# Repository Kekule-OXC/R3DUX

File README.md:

## About this Repository
This is an open source recreation of one of the most well known Original Xbox LPC memory/IO device created by Team Xecuter, the X3/X3-CE.

The VHDL is 100% compatible with All the original TX software including Flashbios and LiveConfig. This allows loading user BIOS binaries and some basic Xbox tools (EEPROM Backup/modification, Hard drive Rebuilding, Locking, Unlocking, FTP access, as well as customizing the colors of the boot animation).  
  
The VHDL written by Team Xecuter was never released and the CPLD is read protected so it is not trivial to extract the bitstream (and they mislabelled the CPLD to make it even more difficult)

While the VHDL is most likely quite different that what was written originally for the X3 my VHDL implementation is fully compatible with all the features of the original chip.
## Background
The R3DUX chip started off as the OpenX3 project in January 2020 with four members of the discussion group for the RE effort, myself (Kekule)  [Team-Donkey](https://github.com/bolwire),  [Ryzee119](https://github.com/Ryzee119),  and [Ernegien](https://github.com/Ernegien).  

We worked for several months and KingLuxor and I completed a schematic based on the original purple X3 chip ([which he released in 2020](https://github.com/bolwire/OpenX3_Public))  with all of their help we identified the components of the PCB and, KingLuxor did the initial part placement, and I did the PCB layout of our initial OpenX3 chip.  

After verifying that the PCB worked (by transplanting all components from a working X3 chip)  the world was hit by the pandemic, and COVID and real life caused the project to fall aside.    

Ergenien was able to extract the majority of the register information need to complete the design, but the real life time demands of virtual work and school there was no time to even start working on the CPLD code.  
 
Time passed and we all went our separate ways, and so with a known working PCB in hand, and a trove of information we had amassed, the project was abandoned.

Fast forward about six months and I decided to start working on it again, and breathed new life into the project, a REDUX as it were.

## Supported Features

R3DUX Features: 

* Purple board color
* Comes from pre-flashed with FlashBIOS utility
* 2MB Flash ROM; can set up 8x256k, 4x512k, 2x1024k or a single 2048k banks
* Dedicated 256k Backup Rom (can be upgraded) 
* i2c Bus for X3 Config LIVE interface to the EEPROM! 
* I/O Bus for Full LCD support 
* Flash Protection Control 
* Mod Enable - Quick Press Power to boot from 2Mb Flash Rom (External LED will indicate BLUE LED) 
* Mod Disable - Press Power >1 second (External LED will indicate RED LED) 
* Quick Press Power+Eject >1 second to boot from 256k Backup Rom (External LED will indicate PURPLE LED) 
* HDD and LAN Activity LEDs
* D0 Control (Disable Mod Via Software) 
* R3DUX works without any switch accessories connected (boots to the first 1MB bank)
* Compatible with all BIOSes 

LCD-Specific Features:
* Custom text Display on boot 
* Display X3 Config Live Version 
* Display Dip switch and selected BIOS
* XBMC and Avalaunch LCD features are compatible

A mix of features from the purple and CE editions
* XLCD connector is a right angle instead of straight
* Single Pinheader for 5v connection on a v1.6 xbox
* Porgramming pins rerouted to the 4 unused pins on the LCD connector instead of test points

## Installation and Initial Setup
Installation is identical to an OEM X3 chip, and all connections are fully compatible so can be used plug and play with a previous X3 install.
 
 Before assembling the board, you must 
 * 1- Program the backup chip with a 256k Flashbios.... 
 * 2- program the main flash chip with a 2MB Flashbios (8 copies).... 
 * 3- program the EEPROM
 * CPLD programming points are wired to the LCD connector (see images folder)
 * JED can be compiled from ISP Lever
See [Installation.MD] for more details

## Licensing
R3DUX gerbers and schematic are free and open source. Please respect the licenses available in their respective folders.
  *  Hardware is shared under the [CERN OHL version 1.2.](https://ohwr.org/cernohl).
  *  Firmware is shared under [GPLv3](https://www.gnu.org/licenses/quick-guide-gplv3.en.html).
 
## References that helped me in this project
  * [Intel LPC Spec](https://www.intel.com/content/dam/www/program/design/us/en/documents/low-pin-count-interface-specification.pdf)
  * [LPC Analyser Plugin](https://github.com/Ryzee119/LPCAnalyzer)  
  * [Deconstructing the Xbox Boot ROM](https://mborgerson.com/deconstructing-the-xbox-boot-rom/)

By Kekule

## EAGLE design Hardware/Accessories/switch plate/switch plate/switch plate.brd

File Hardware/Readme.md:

| Qty | Value                   | Device           | Package                    | Parts          | Description                 | DigiKey Part         |
|-----|-------------------------|------------------|----------------------------|----------------|-----------------------------|----------------------|
| 2   | Blue                    | LED              | 805                        | LED1, LED2     | LED                         | 1516-1083-1-ND       |
| 1   |                         | PINHD-1X1        | 1X01                       | JP2            | PIN HEADER                  |                      |
| 1   |                         | PINHD-2X8        | 2X08                       | JP1            | PIN HEADER                  |                      |
| 1   | 0                       | Resistor         | 0603                       | R7             | 0ohm resistor               | 541-3927-1-ND        |
| 2   | 0.1uF                   | CAP              | 603                        | C1, C2         |  Ceramic Capacitors         | 720-1689-1-ND        |
| 1   | 0532610271              | 2P connector     | MOLEX_0532610271           | J3             | 1.25mm Pitch PicoBlade      | WM7620CT-ND          |
| 1   | 0532610371              | 3P connector     | MOLEX_0532610371           | J4             | 1.25mm Pitch PicoBlade      | WM7621CT-ND          |
| 1   | 100                     | RES ARRAY        | 0603-ARV                   | RN3            | Array Chip Resistor         | 42X083101JPCT-ND     |
| 3   | 10k                     | RES              | 0603                       | R5, R6, R8     | 10kohm resistor             | PAT10KACT-ND         |
| 2   | 10k                     | RES ARRAY        | 0603-ARV                   | RN1, RN2       | Array Chip Resistor         | TC164J-10KCT-ND      |
| 2   | 200                     | RES              | 0603                       | R9, R10        | 200ohm resistor             | P200GCT-ND           |
| 1   | AT24C08                 | EEPROM           | SO-08                      | IC1            | Serial EEPROM               | AT24C08D-SSHM-B-ND   |
| 1   | 4.7k                    | RES              | 0603                       | R12            | 4.7kohm resistor            | 541-3689-1-ND        |
| 1   | AM29F002BB90EI          | FLASH            | TS032                      | U3             | NOR Flash 5V 2Mbit          | -----                |
| 1   | AM29F016D-70EF          | FLASH            | SOP50P2000X120-48N         | U2             | NOR Flash 5V 16Mbit         | -----                |
| 1   | 10k                     | POT              | TRIM_F09                   | R11            | Thumbwheel Pot 10mm         | -----                |
| 1   | LC4256V-75TN100C        | LC4256V-75TN100C | TQFP100                    | U1             | Lattice MACH4000 CPLD 256MC | 220-1706-ND          |
| 1   | PCM12SMTR               | PCM12SMTR        | SW_PCM12SMTR               | S1             | SPDT Side                   | 401-2016-1-ND        |
| 4   | SI1967DH-T1-GE3         | PNP-Transistor   | TRANS_UM6J1-L              | R1, R2, R3, R4 |                             | SI1967DH-T1-GE3CT-ND |
| 1   | SM12B-SRSS-TB(LF)(SN)   | 12P JST          | CONN_SM12B-SRSS-TB(LF)(SN) | J2             |                             | 455-1812-1-ND        |
| 1   | SM20B-SRDS-G-TF(LF)(SN) | 20P JST          | SM20BSRDSGTFLFSN           | J1             | JST SHD, 1mm Pitch          | 455-1866-1-ND        |

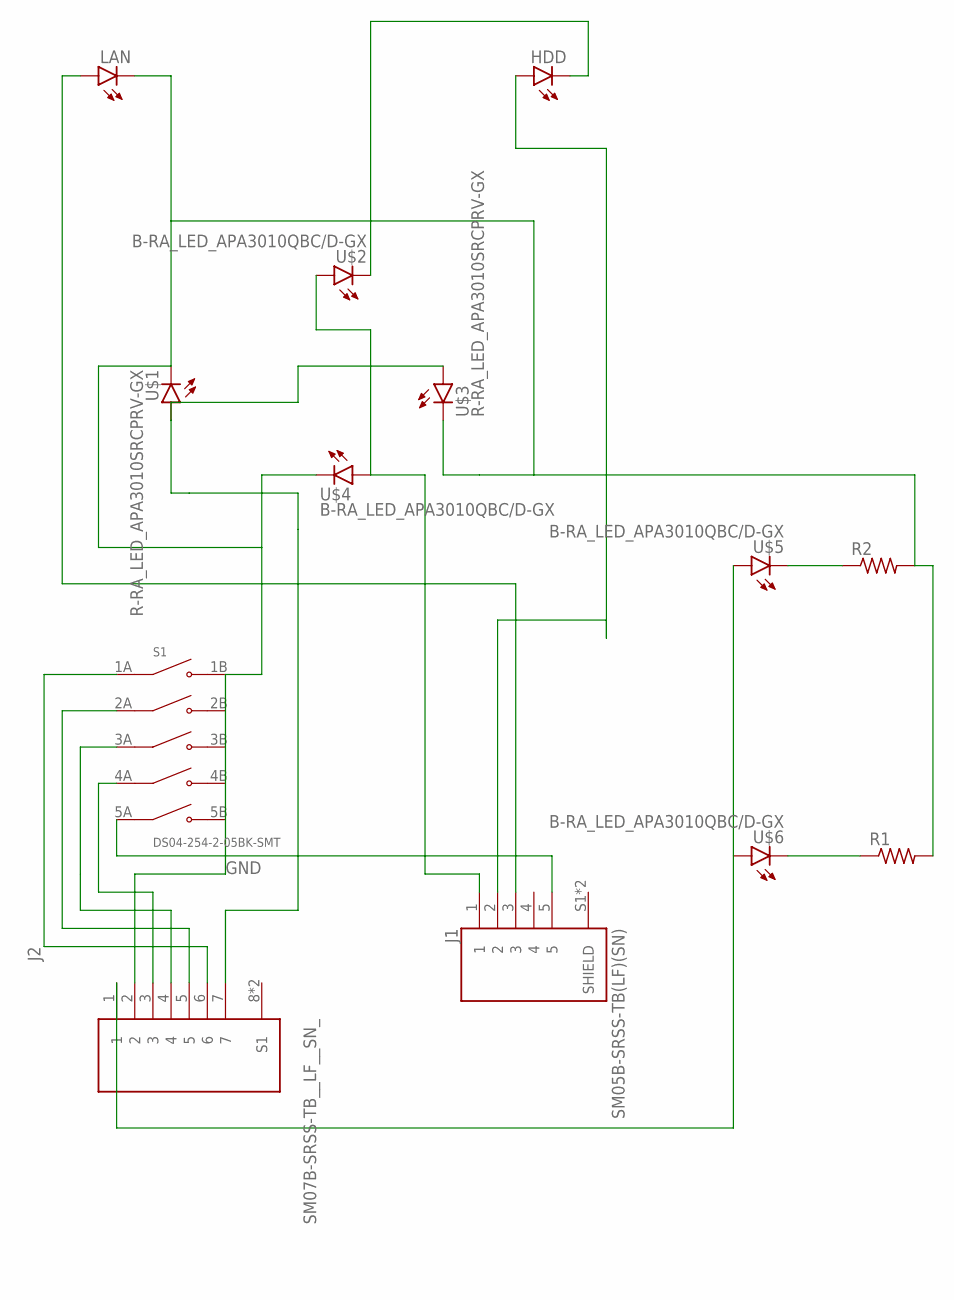
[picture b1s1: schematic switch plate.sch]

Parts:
HDD: LEDCHIP-LED0603; CHIP-LED0603
J1: SM05B-SRSS-TB(LF)(SN); JST_SM05B-SRSS-TB(LF)(SN)
J2: SM07B-SRSS-TB__LF__SN_; SM07B-SRSS-TB
LAN: LEDCHIP-LED0603; CHIP-LED0603
R1, R2: R-US_R0603; R0603
S1: DS04-254-2-05BK-SMT; SW_DS04-254-2-05BK-SMT
U$1, U$3: R-RA_LED_APA3010SRCPRV-GX; APBA3010ESGC
U$2, U$4, U$5, U$6: B-RA_LED_APA3010QBC/D-GX; APBA3010ESGC

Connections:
GND: HDD.C, J2.2, LAN.C, R1.2, R2.2, S1.1B (NO1), S1.2B (NO2), S1.3B (NO3), S1.4B (NO4), S1.5B (NO5), U$1.3 (C), U$2.3 (C), U$3.3 (C), U$4.3 (C)
unnamed: J2.1, U$5.1 (A), U$6.1 (A)
unnamed: J2.3, S1.4A (COM4)
unnamed: J2.4, S1.3A (COM3)
unnamed: J2.5, S1.2A (COM2)
unnamed: J2.6, S1.1A (COM1)
unnamed: J2.7, U$1.1 (A), U$3.1 (A)
unnamed: J1.1, U$2.1 (A), U$4.1 (A)
unnamed: HDD.A, J1.2
unnamed: J1.3, LAN.A
unnamed: J1.5, S1.5A (COM5)
unnamed: R2.1, U$5.3 (C)
unnamed: R1.1, U$6.3 (C)

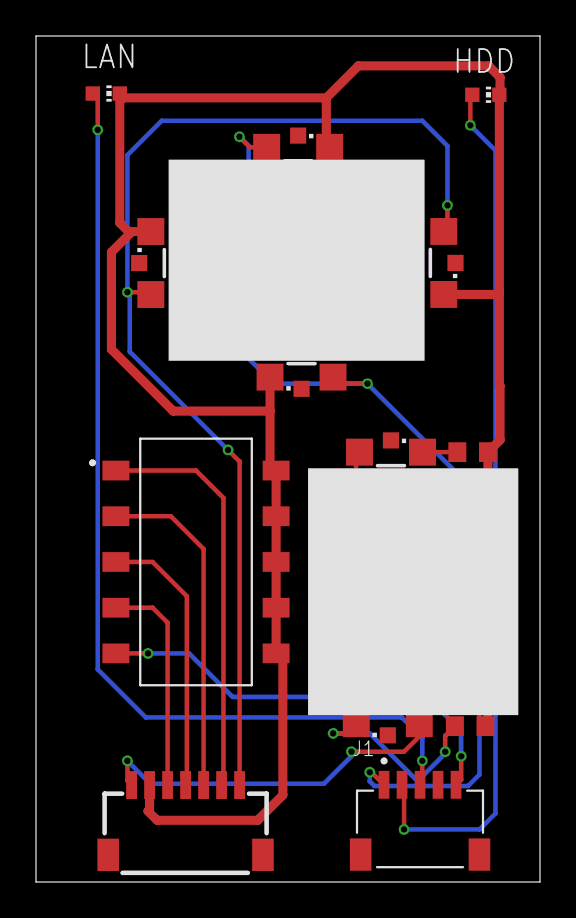
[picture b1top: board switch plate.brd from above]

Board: 2 copper layers, 28.0 x 47.0 mm, 13 parts (0 on the bottom side), 13 nets.

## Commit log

2021-05-24 Create t
2021-05-25 Create Readme.md
    added main board BOM
2021-07-03 Create test
2021-07-03 Add files via upload
    files for flash chip and eeprom
2023-05-03 Update r3dux.vhd
    recovered from NAS. I think this is the most complete version
2025-12-05 think working
2025-12-05 Added ignore
2025-12-05 Added: flashcat file
2025-12-05 fixed no switch bank size
2026-06-12 added missing blanked x3 eeprom image
